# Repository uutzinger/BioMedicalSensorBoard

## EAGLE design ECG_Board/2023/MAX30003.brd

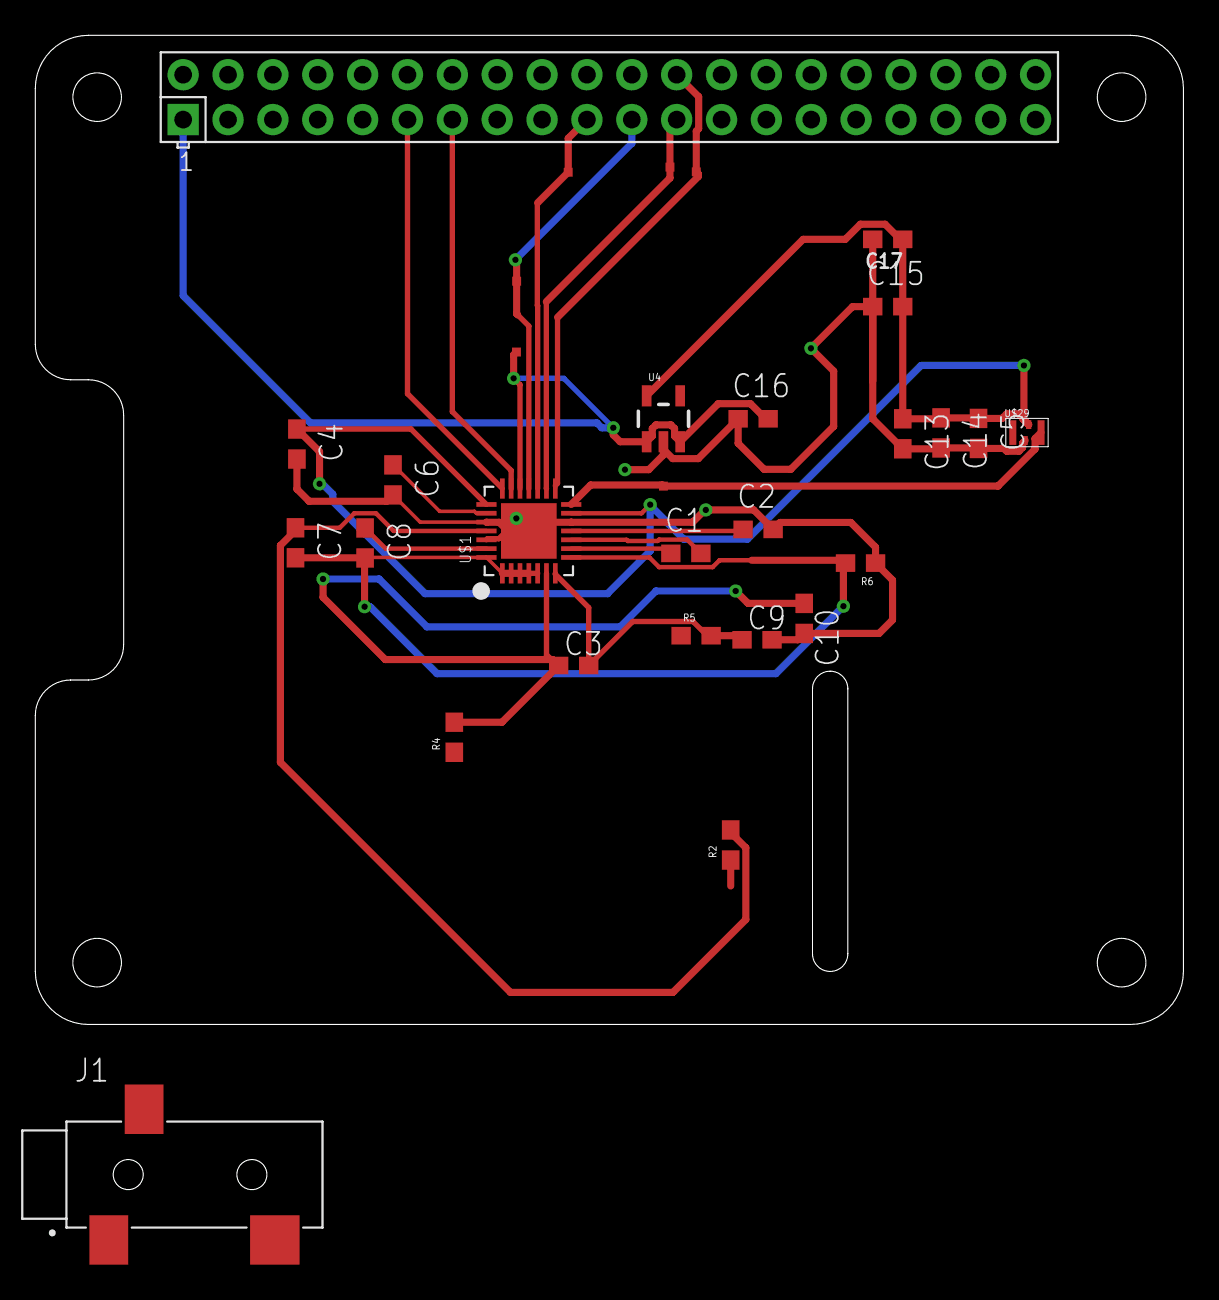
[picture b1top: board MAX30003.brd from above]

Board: 2 copper layers, 65.0 x 56.0 mm, 30 parts (0 on the bottom side), 22 nets.

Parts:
C1, C5, C8, C13, C15, C16, C17: 1.0uF; 0603
C2, C3, C9, C10: 1nF; 0603
C4, C6, C7, C14: 10uF; 0603
J1: SJ-3523-SMT-TR; CUI_SJ-3523-SMT-TR
R2, R6: 0.05; 0603
R4, R5: 47k; 0603
TP1, TP2, TP3, TP5, TP6, TP8: TEST-POINT2; PAD.02X.02
U4: AP2112K-1.8V; SOT23-5
U$1: MAX30003CTI+; QFN-28
U$29: SIT1533
X1: RASPI_BOARD_B+_HDC; RASPI_BOARD_B+HAT_DF_CF

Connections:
+1.8V: C4.1, C5.1, C13.1, C14.1, C15.2, C17.1, U4.5, U$1.13, U$1.22, U$29.4
AGND: C7.2, C8.2, R6.2, U$1.1, U$1.2, U$1.3, U$1.4, U$1.5, U$1.8, U$1.28
CSB: TP3.P$1, U$1.15, X1.24
ECGN: C3.2, C9.1, R5.2, U$1.7
ECGP: C3.1, C10.1, R4.2, U$1.6
FCLK: TP5.P$1, U$1.14, U$29.3, X1.7
GND: C2.2, C4.2, C5.2, C6.2, C9.2, C10.2, C13.2, C14.2, C15.1, C16.1, C17.2, R6.1, U4.2, U$1.12, U$1.24, U$1.26, U$1.THERMAL, U$29.2
INT2B: U$1.20, X1.13
INTB: U$1.21, X1.11
MISO: TP2.P$1, U$1.18, X1.21
MOSI: TP1.P$1, U$1.17, X1.19
unnamed: J1.3, R4.1
unnamed: C6.1, U$1.23
unnamed: C1.1, U$1.9
unnamed: J1.1, R2.1
unnamed: C1.2, U$1.10
unnamed: C2.1, U$1.11
unnamed: J1.2, R5.1
unnamed: C8.1, U$1.27
SCLK: TP8.P$1, U$1.16, X1.23
VCM: C7.1, R2.2, U$1.25
VDD: C16.2, TP6.P$1, U4.1, U4.3, U$1.19, X1.1

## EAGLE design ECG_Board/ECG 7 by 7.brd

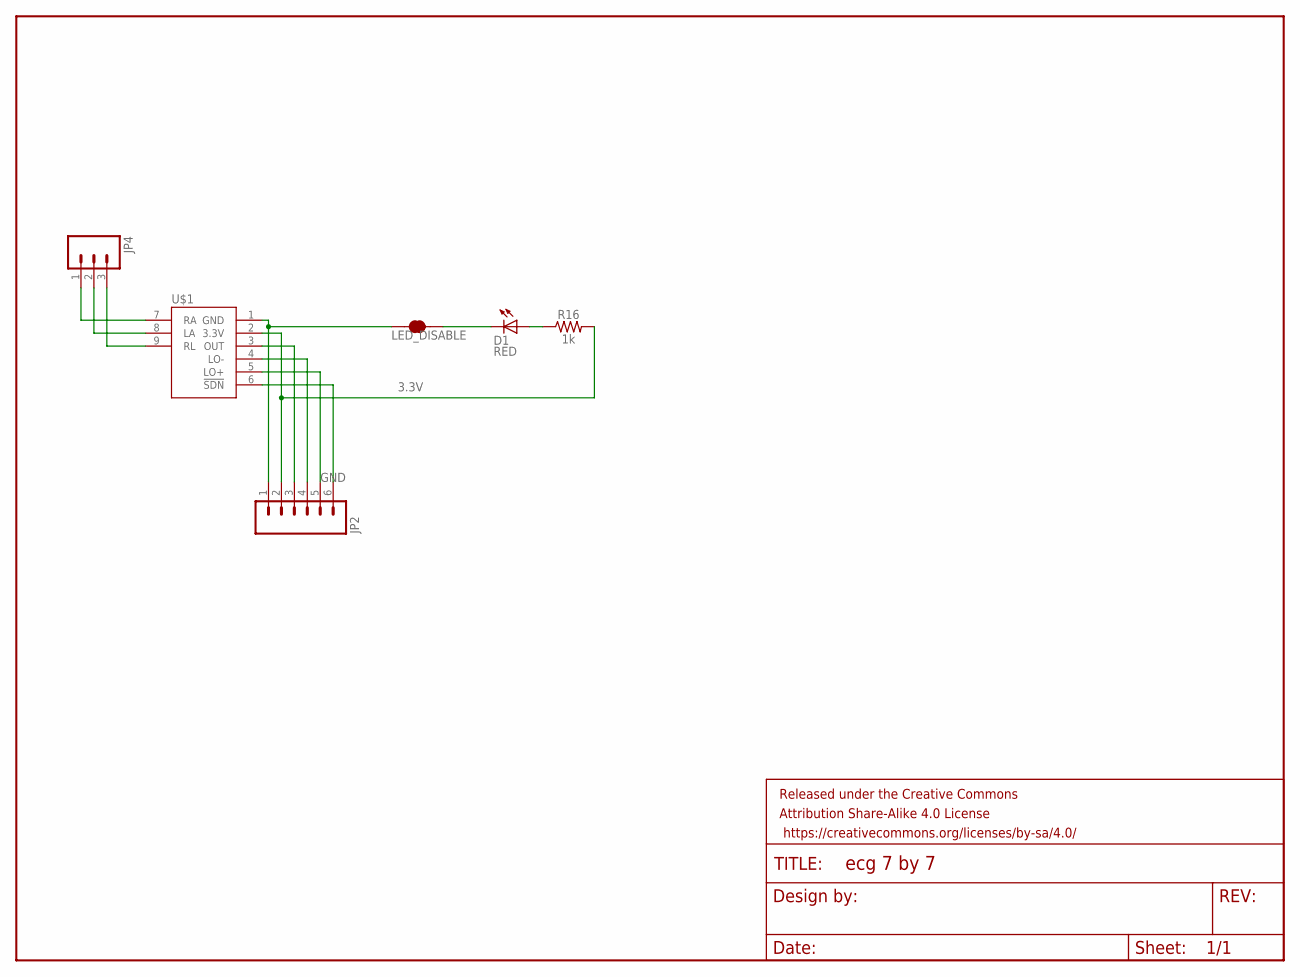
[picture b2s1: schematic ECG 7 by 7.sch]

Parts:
D1: RED; LED-0603
FRAME1: FRAME-LETTERNO_PACKAGE; DUMMY
JP2: M06SIP; 1X06
JP4: M03PTH; 1X03
LED_DISABLE: JUMPER-SMT_2_NC_TRACE_SILK; SMT-JUMPER_2_NC_TRACE_SILK
R16: 1k; 0603
U$1: SPARK_ECG

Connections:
3.3V: JP2.2, R16.2, U$1.2 (3.3V)
GND: JP2.1, LED_DISABLE.1, U$1.1 (GND)
unnamed: JP4.1, U$1.7 (RA)
unnamed: JP4.2, U$1.8 (LA)
unnamed: JP4.3, U$1.9 (RL)
unnamed: JP2.6, U$1.6 (!SDN)
unnamed: JP2.5, U$1.5 (LO+)
unnamed: JP2.4, U$1.4 (LO-)
unnamed: JP2.3, U$1.3 (OUT)
unnamed: D1.A, R16.1
unnamed: D1.C, LED_DISABLE.2

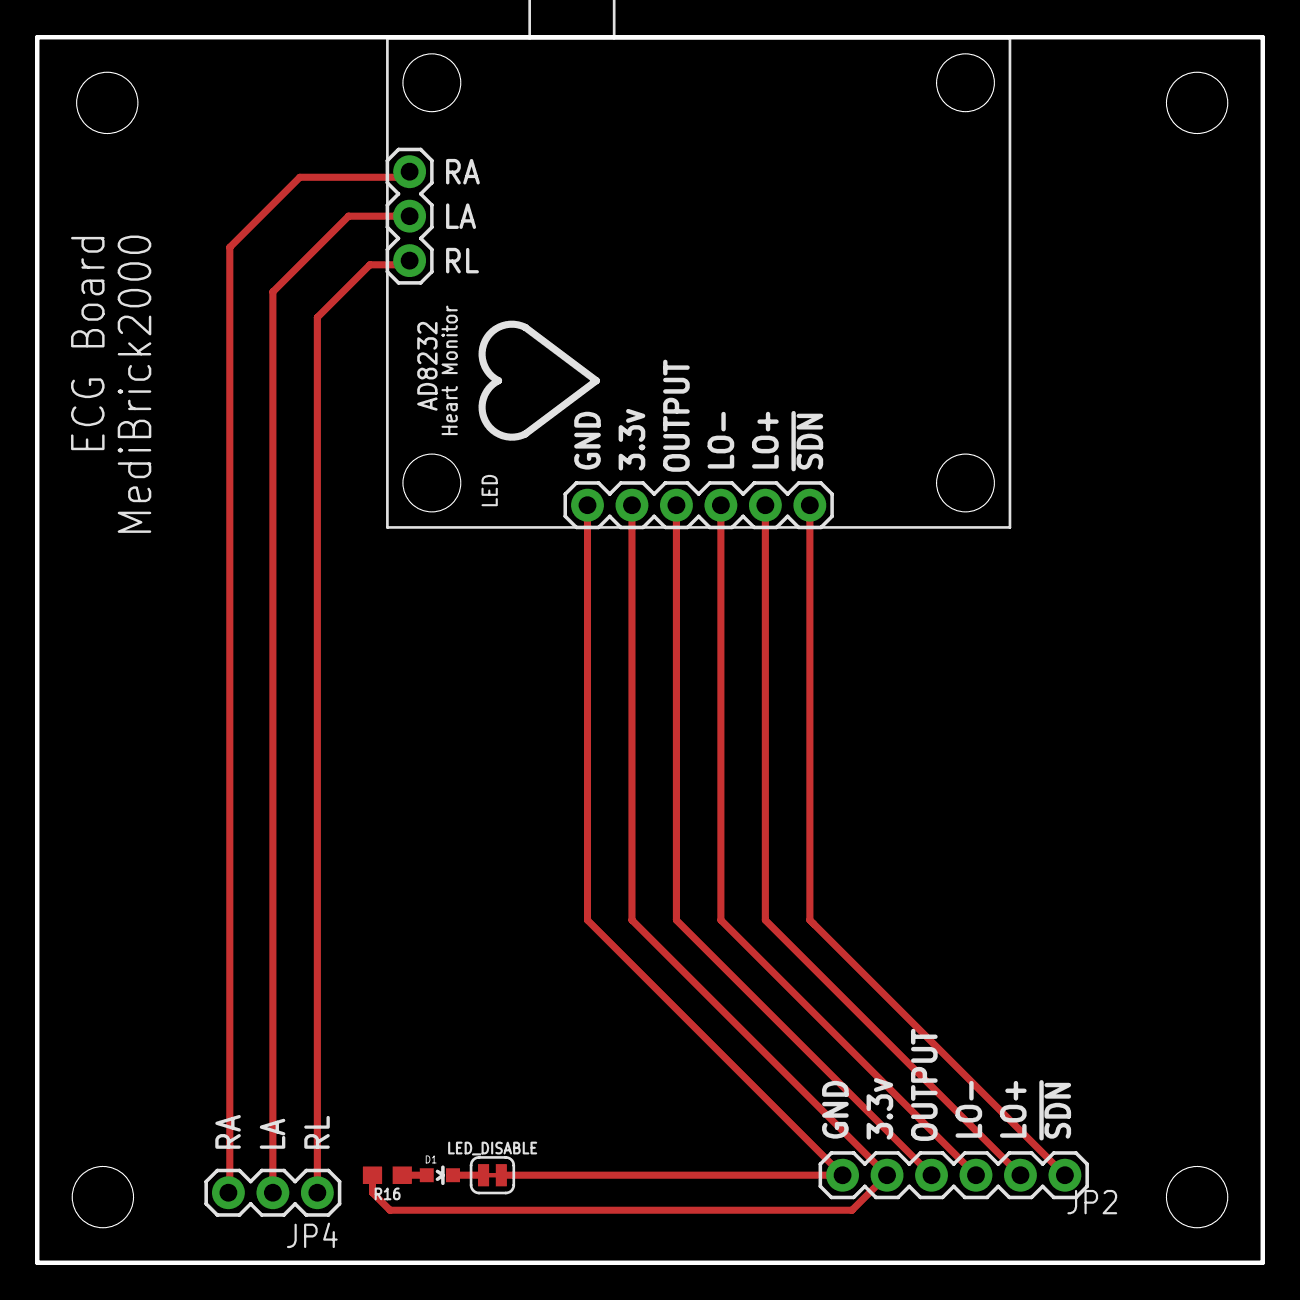
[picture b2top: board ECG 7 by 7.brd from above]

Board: 2 copper layers, 70.0 x 70.0 mm, 7 parts (0 on the bottom side), 11 nets.

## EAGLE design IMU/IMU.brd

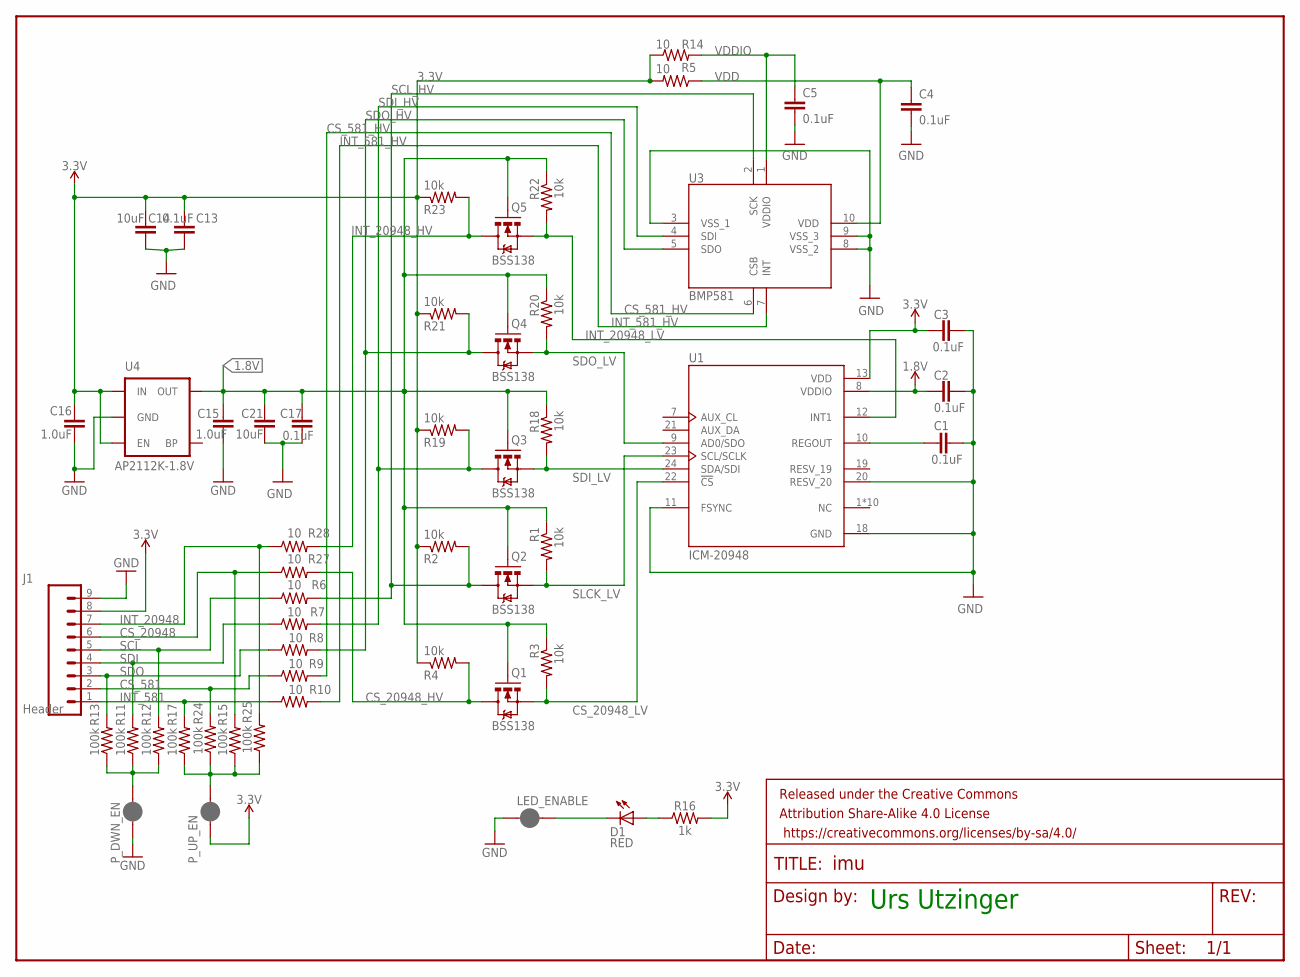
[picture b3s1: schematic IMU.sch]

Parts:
C1, C2, C3, C4, C5, C13, C17: 0.1uF; 0603
C14, C21: 10uF; 0603@1
C15, C16: 1.0uF; 0603
D1: RED; LED-0603
FRAME1: FRAME-LETTERNO_PACKAGE; DUMMY
J1: Header; 1X09
LED_ENABLE: LED ENABLE; SMT-JUMPER_2_NC_PASTE_SILK
P_DWN_EN: JUMPER-SMT_2_NC_PASTE_SILK; SMT-JUMPER_2_NC_PASTE_SILK
P_UP_EN: JUMPER-SMT_2_NC_PASTE_SILK; SMT-JUMPER_2_NC_PASTE_SILK
Q1, Q2, Q3, Q4, Q5: BSS138; SPARKFUN_SOT23-3
R1, R2, R3, R4, R18, R19, R20, R21, R22, R23: 10k; 0603
R5, R6, R7, R8, R9, R10, R14, R27, R28: 10; 0603
R11, R12, R13, R15, R17, R24, R25: 100k; 0603
R16: 1k; 0603
U1: ICM-20948; QFN40P300X300X105-24N
U3: BMP581
U4: AP2112K-1.8V; SOT23-5

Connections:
1.8V: C2.1, C15.2, C17.1, C21.1, Q1.1 (G), Q2.1 (G), Q3.1 (G), Q4.1 (G), Q5.1 (G), R1.1, R3.1, R18.1, R20.1, R22.1, U1.8 (VDDIO), U4.5 (OUT)
3.3V: C3.1, C13.1, C14.1, C16.2, J1.8, P_UP_EN.1, R2.1, R4.1, R5.2, R14.1, R16.2, R19.1, R21.1, R23.1, U1.13 (VDD), U4.1 (IN), U4.3 (EN)
CS_581: J1.2, R9.1, R24.2
CS_581_HV: R9.2, U3.6 (CSB)
CS_20948: J1.6, R15.2, R27.1
CS_20948_HV: Q1.3 (D), R4.2, R27.2
CS_20948_LV: Q1.2 (S), R3.2, U1.22 (!CS)
GND: C1.2, C2.2, C3.2, C4.2, C5.2, C13.2, C14.2, C15.1, C16.1, C17.2, C21.2, J1.9, LED_ENABLE.1, P_DWN_EN.1, U1.11 (FSYNC), U1.18 (GND), U1.20 (RESV_20), U3.3 (VSS_1), U3.8 (VSS_2), U3.9 (VSS_3), U4.2 (GND)
INT_581: J1.1, R10.1, R17.2
INT_581_HV: R10.2, U3.7 (INT)
INT_20948: J1.7, R25.2, R28.1
INT_20948_HV: Q5.3 (D), R23.2, R28.2
INT_20948_LV: Q5.2 (S), R22.2, U1.12 (INT1)
unnamed: C1.1, U1.10 (REGOUT)
unnamed: D1.A, R16.1
unnamed: D1.C, LED_ENABLE.2
unnamed: P_DWN_EN.2, R11.1, R12.1, R13.1
unnamed: P_UP_EN.2, R15.1, R17.1, R24.1, R25.1
SCL: J1.5, R6.1, R12.2
SCL_HV: Q2.3 (D), R2.2, R6.2, U3.2 (SCK)
SDI: J1.4, R7.1, R11.2
SDI_HV: Q3.3 (D), R7.2, R19.2, U3.4 (SDI)
SDI_LV: Q3.2 (S), R18.2, U1.24 (SDA/SDI)
SDO: J1.3, R8.1, R13.2
SDO_HV: Q4.3 (D), R8.2, R21.2, U3.5 (SDO)
SDO_LV: Q4.2 (S), R20.2, U1.9 (AD0/SDO)
SLCK_LV: Q2.2 (S), R1.2, U1.23 (SCL/SCLK)
VDD: C4.1, R5.1, U3.10 (VDD)
VDDIO: C5.1, R14.2, U3.1 (VDDIO)

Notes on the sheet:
Urs Utzinger

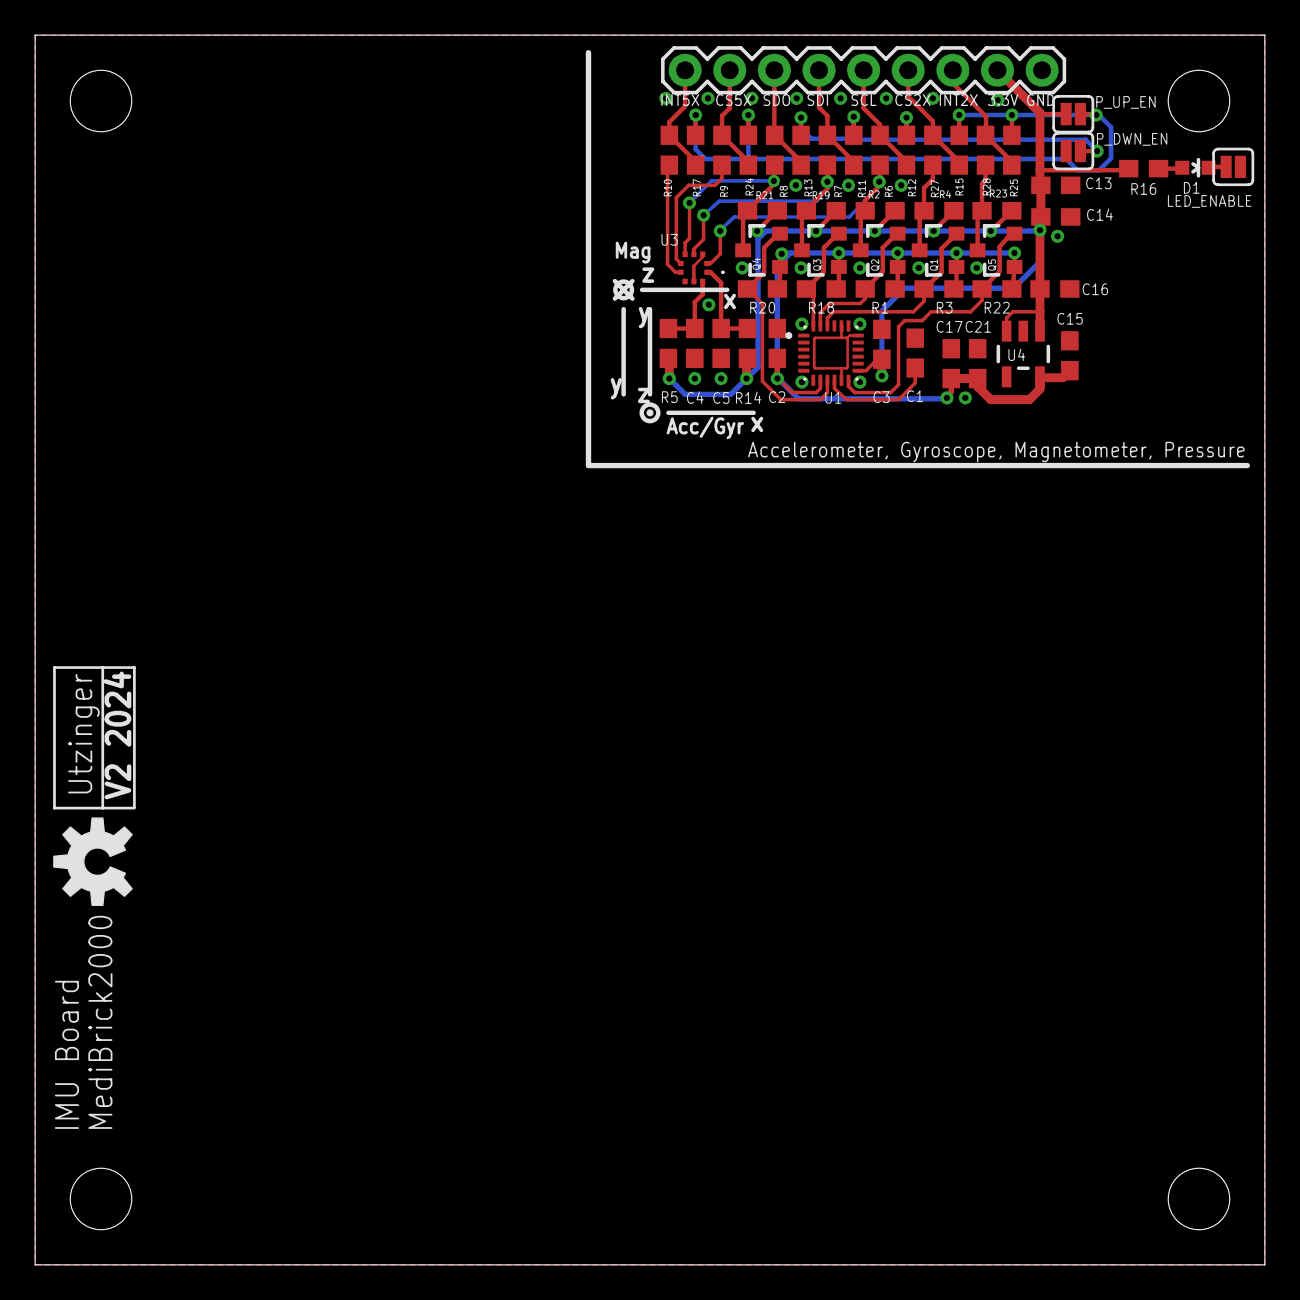
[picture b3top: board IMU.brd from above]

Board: 2 copper layers, 70.0 x 70.0 mm, 53 parts (0 on the bottom side), 29 nets.

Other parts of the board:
U$1: OSHW-LOGO-M

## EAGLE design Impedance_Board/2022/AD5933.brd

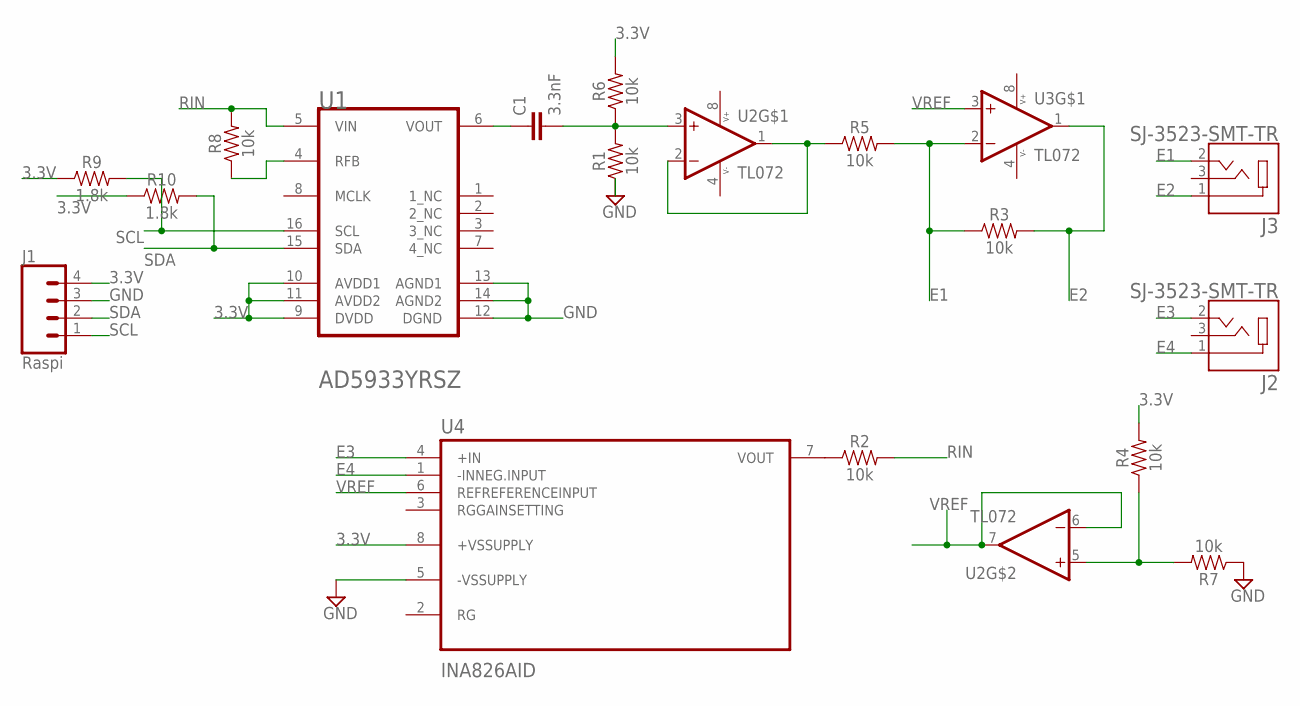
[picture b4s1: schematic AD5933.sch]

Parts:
C1: 3.3nF; 0603
J1: Raspi; 1X04
J2, J3: SJ-3523-SMT-TR; CUI_SJ-3523-SMT-TR
R1, R2, R3, R4, R5, R6, R7, R8: 10k; 0603
R9, R10: 1.8k; 0603
U1: ANALOG_DEVICES_AD5933YRSZANALOG_DEVICES_AD5933YRS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; ANALOG_DEVICES_AD5933YRSZ_0
U2, U3: TL072; SOIC127P600X175-8N
U4: INA826AID; SOIC127P599X175-8N

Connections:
3.3V: J1.4, R4.2, R6.2, R9.1, R10.1, U1.9 (DVDD), U1.10 (AVDD1), U1.11 (AVDD2), U4.8 (+VSSUPPLY)
E1: J3.2, R3.1, R5.2, U3.2 (-IN1)
E2: J3.1, R3.2, U3.1 (OUT1)
E3: J2.2, U4.4 (+IN)
E4: J2.1, U4.1 (-INNEG.INPUT)
GND: J1.3, R1.1, R7.1, U1.12 (DGND), U1.13 (AGND1), U1.14 (AGND2), U4.5 (-VSSUPPLY)
unnamed: R2.1, U4.7 (VOUT)
unnamed: C1.1, U1.6 (VOUT)
unnamed: C1.2, R1.2, R6.1, U2.3 (+IN1)
unnamed: R5.1, U2.1 (OUT1), U2.2 (-IN1)
unnamed: R8.1, U1.4 (RFB)
unnamed: R4.1, R7.2, U2.5 (+IN2)
RIN: R2.2, R8.2, U1.5 (VIN)
SCL: J1.1, R9.2, U1.16 (SCL)
SDA: J1.2, R10.2, U1.15 (SDA)
V+: U2.8 (V+), U3.8 (V+)
V-: U2.4 (V-), U3.4 (V-)
VREF: U2.6 (-IN2), U2.7 (OUT2), U3.3 (+IN1), U4.6 (REFREFERENCEINPUT)

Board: 2 copper layers, 18 parts (0 on the bottom side), 18 nets, no tracks yet.

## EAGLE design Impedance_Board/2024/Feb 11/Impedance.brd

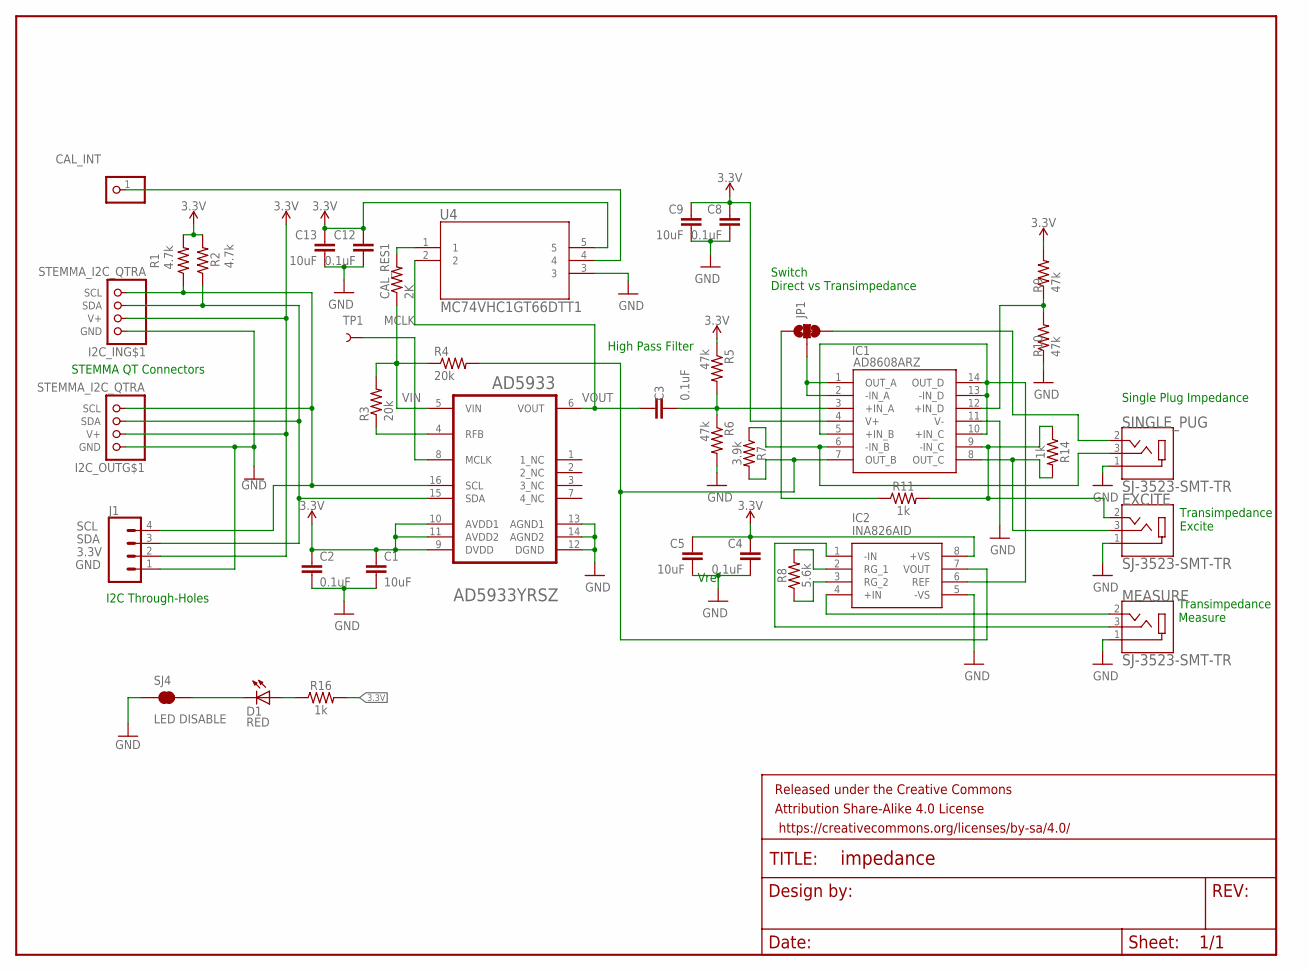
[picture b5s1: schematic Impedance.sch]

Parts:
AD5933: ANALOG_DEVICES_AD5933YRSZANALOG_DEVICES_AD5933YRS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; ANALOG_DEVICES_AD5933YRSZ_0
C1, C5, C9, C13: 10uF; C0603
C2, C4, C8, C12: 0.1uF; C0603
C3: 0.1uF; 0603
CAL_INT: PINHD-1X1; 1X01
CAL_RES1: 2K; R0603
D1: RED; LED-0603
EXCITE: SJ-3523-SMT-TR; CUI_SJ-3523-SMT-TR
FRAME1: FRAME-LETTERNO_PACKAGE; DUMMY
I2C_IN, I2C_OUT: STEMMA_I2C_QTRA; JST_SH4_RA
IC1: AD8608ARZ; SOIC127P600X175-14N
IC2: INA826AID; SOIC127P600X175-8N
J1: CONN_04; 1X04
JP1: JUMPER-SMT_3_1-NC_TRACE_NO-SILK; SMT-JUMPER_3_1-NC_TRACE_NO-SILK
MEASURE: SJ-3523-SMT-TR; CUI_SJ-3523-SMT-TR
R1, R2: 4.7k; 0603
R3, R4: 20k; 0603
R5, R6, R9, R10: 47k; 0603
R7: 3.9k; 0603
R8: 5.6k; 0603
R11, R14, R16: 1k; 0603
SINGLE_PUG: SJ-3523-SMT-TR; CUI_SJ-3523-SMT-TR
SJ4: LED DISABLE; SMT-JUMPER_2_NC_TRACE_NO-SILK
TP1: TEST-POINT3X5; PAD.03X.05
U4: MC74VHC1GT66DTT1; TSOP5_1P65X3P15_ONS

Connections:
3.3V: AD5933.9 (DVDD), AD5933.10 (AVDD1), AD5933.11 (AVDD2), C1.1, C2.1, C4.1, C5.1, C8.1, C9.1, C12.1, C13.1, I2C_IN.2 (V+), I2C_OUT.2 (V+), IC1.4 (V+), IC2.8 (+VS), J1.2, R1.2, R2.2, R5.1, R9.2, R16.2, U4.5
GND: AD5933.12 (DGND), AD5933.13 (AGND1), AD5933.14 (AGND2), C1.2, C2.2, C4.2, C5.2, C8.2, C9.2, C12.2, C13.2, EXCITE.1, I2C_IN.1 (GND), I2C_OUT.1 (GND), IC1.11 (V-), IC2.5 (-VS), J1.1, MEASURE.1, R6.2, R10.1, SINGLE_PUG.1, SJ4.1, U4.3
MCLK: AD5933.8 (MCLK), TP1.P$1
unnamed: IC1.6 (-IN_B), R7.1, SINGLE_PUG.3
unnamed: CAL_INT.1, U4.4
unnamed: AD5933.4 (RFB), R3.1
unnamed: C3.2, IC1.3 (+IN_A), R5.2, R6.1
unnamed: JP1.1, R11.1
unnamed: IC1.1 (OUT_A), IC1.2 (-IN_A), JP1.2
unnamed: IC1.7 (OUT_B), IC2.7 (VOUT), R4.2, R7.2
unnamed: IC1.12 (+IN_D), R9.1, R10.2
unnamed: JP1.3, SINGLE_PUG.2
unnamed: IC1.5 (+IN_B), IC1.10 (+IN_C), IC1.13 (-IN_D), IC1.14 (OUT_D), IC2.6 (REF)
unnamed: EXCITE.2, IC1.9 (-IN_C), R11.2, R14.1
unnamed: IC2.4 (+IN), MEASURE.2
unnamed: IC2.1 (-IN), MEASURE.3
unnamed: IC2.2 (RG_1), R8.2
unnamed: IC2.3 (RG_2), R8.1
unnamed: CAL_RES1.2, U4.1
unnamed: EXCITE.3, IC1.8 (OUT_C), R14.2
unnamed: D1.A, R16.1
unnamed: D1.C, SJ4.2
SCL: AD5933.16 (SCL), I2C_IN.4 (SCL), I2C_OUT.4 (SCL), J1.4, R1.1
SDA: AD5933.15 (SDA), I2C_IN.3 (SDA), I2C_OUT.3 (SDA), J1.3, R2.1
VIN: AD5933.5 (VIN), CAL_RES1.1, R3.2, R4.1
VOUT: AD5933.6 (VOUT), C3.1, U4.2

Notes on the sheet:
High Pass Filter
Vref
Transimpedance Measure
Transimpedance Excite
Single Plug Impedance
STEMMA QT Connectors
I2C Through-Holes
Switch Direct vs Transimpedance

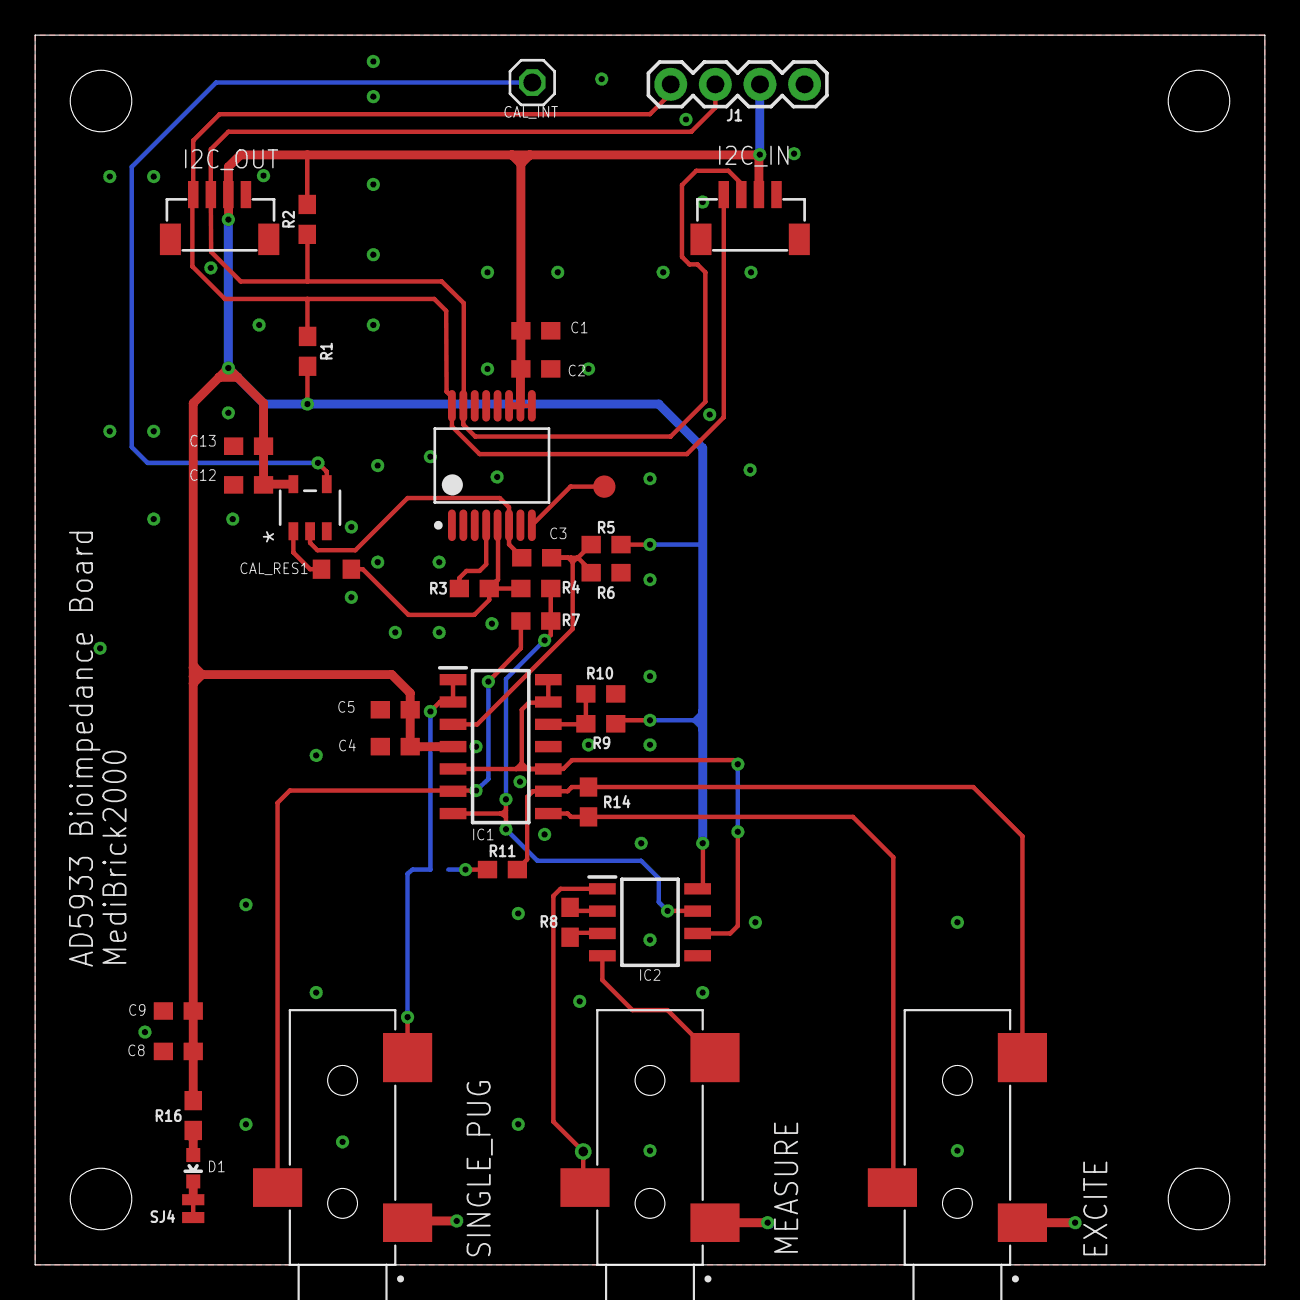
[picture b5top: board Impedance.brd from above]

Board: 2 copper layers, 70.0 x 70.0 mm, 39 parts (1 on the bottom side), 26 nets.

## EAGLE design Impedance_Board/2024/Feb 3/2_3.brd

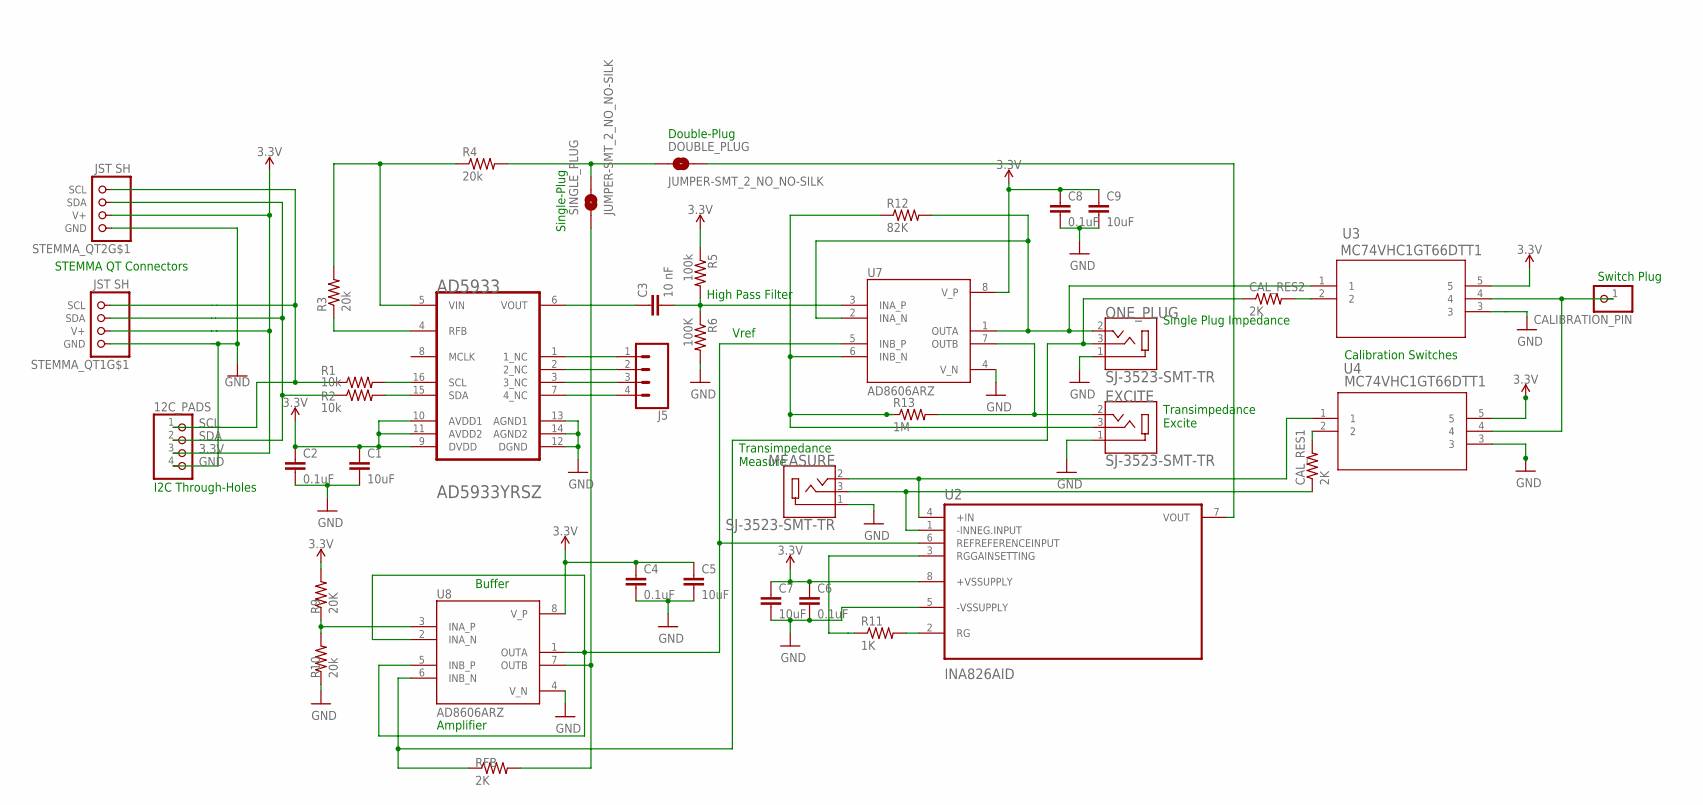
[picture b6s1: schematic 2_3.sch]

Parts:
12C_PADS: PINHD-1X4; 1X04
AD5933: ANALOG_DEVICES_AD5933YRSZANALOG_DEVICES_AD5933YRS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; ANALOG_DEVICES_AD5933YRSZ_0
C1, C5, C7, C9: 10uF; C0603
C2, C4, C6, C8: 0.1uF; C0603
C3: 10 nF; C0603
CALIBRATION_PIN: PINHD-1X1; 1X01
CAL_RES1, CAL_RES2: 2K; R0603
DOUBLE_PLUG: JUMPER-SMT_2_NO_NO-SILK; SMT-JUMPER_2_NO_NO-SILK
EXCITE: SJ-3523-SMT-TR; CUI_SJ-3523-SMT-TR
J5: CONN_04; 1X04
MEASURE: SJ-3523-SMT-TR; CUI_SJ-3523-SMT-TR
ONE_PLUG: SJ-3523-SMT-TR; CUI_SJ-3523-SMT-TR
R1, R2: 10k; R0603
R3, R4, R10: 20k; R0603
R5: 100k; R0603
R6: 100K; R0603
R9: 20K; R0603
R11: 1K; R0603
R12: 82K; R0603
R13: 1M; R0603
RFB: 2K; R0603
SINGLE_PLUG: JUMPER-SMT_2_NO_NO-SILK; SMT-JUMPER_2_NO_NO-SILK
STEMMA_QT1, STEMMA_QT2: JST SH; JST_SH4_RA
U2: INA826AID; SOIC127P599X175-8N
U3, U4: MC74VHC1GT66DTT1; TSOP5_1P65X3P15_ONS
U7, U8: AD8606ARZ; SOIC127P600X175-8N

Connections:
3.3V: 12C_PADS.3, AD5933.9 (DVDD), AD5933.10 (AVDD1), AD5933.11 (AVDD2), C1.1, C2.1, C4.1, C5.1, C6.1, C7.1, C8.1, C9.1, R5.1, R9.2, STEMMA_QT1.2 (V+), STEMMA_QT2.2 (V+), U2.8 (+VSSUPPLY), U3.5, U4.5, U7.8 (V_P), U8.8 (V_P)
GND: 12C_PADS.4, AD5933.12 (DGND), AD5933.13 (AGND1), AD5933.14 (AGND2), C1.2, C2.2, C4.2, C5.2, C6.2, C7.2, C8.2, C9.2, EXCITE.1, MEASURE.1, ONE_PLUG.1, R6.2, R10.1, STEMMA_QT1.1 (GND), STEMMA_QT2.1 (GND), U2.5 (-VSSUPPLY), U3.3, U4.3, U7.4 (V_N), U8.4 (V_N)
unnamed: AD5933.16 (SCL), R1.2
unnamed: AD5933.15 (SDA), R2.2
unnamed: AD5933.1 (1_NC), J5.1
unnamed: AD5933.2 (2_NC), J5.2
unnamed: AD5933.4 (RFB), R3.1
unnamed: AD5933.5 (VIN), R3.2, R4.1
unnamed: DOUBLE_PLUG.1, R4.2, SINGLE_PLUG.2
unnamed: AD5933.6 (VOUT), C3.1
unnamed: C3.2, R5.2, R6.1, U7.3 (INA_P)
unnamed: AD5933.3 (3_NC), J5.3
unnamed: AD5933.7 (4_NC), J5.4
unnamed: RFB.2, SINGLE_PLUG.1, U8.7 (OUTB)
unnamed: U2.6 (REFREFERENCEINPUT), U7.5 (INB_P), U8.1 (OUTA), U8.2 (INA_N), U8.5 (INB_P)
unnamed: R9.1, R10.2, U8.3 (INA_P)
unnamed: ONE_PLUG.2, R12.2, U3.1, U7.1 (OUTA), U7.2 (INA_N)
unnamed: R11.1, U2.3 (RGGAINSETTING)
unnamed: CAL_RES2.1, ONE_PLUG.3, RFB.1, U8.6 (INB_N)
unnamed: R11.2, U2.2 (RG)
unnamed: EXCITE.2, R13.2, U7.7 (OUTB)
unnamed: MEASURE.2, U2.4 (+IN), U4.1
unnamed: CAL_RES1.1, MEASURE.3, U2.1 (-INNEG.INPUT)
unnamed: CAL_RES2.2, U3.2
unnamed: EXCITE.3, R12.1, R13.1, U7.6 (INB_N)
unnamed: CAL_RES1.2, U4.2
unnamed: DOUBLE_PLUG.2, U2.7 (VOUT)
unnamed: CALIBRATION_PIN.1, U3.4, U4.4
SCL: 12C_PADS.1, R1.1, STEMMA_QT1.4 (SCL), STEMMA_QT2.4 (SCL)
SDA: 12C_PADS.2, R2.1, STEMMA_QT1.3 (SDA), STEMMA_QT2.3 (SDA)

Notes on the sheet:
High Pass Filter
Vref
Transimpedance Measure
Transimpedance Excite
Single Plug Impedance
Amplifier
Buffer
Switch Plug
Calibration Switches
STEMMA QT Connectors
I2C Through-Holes
Single-Plug
Double-Plug

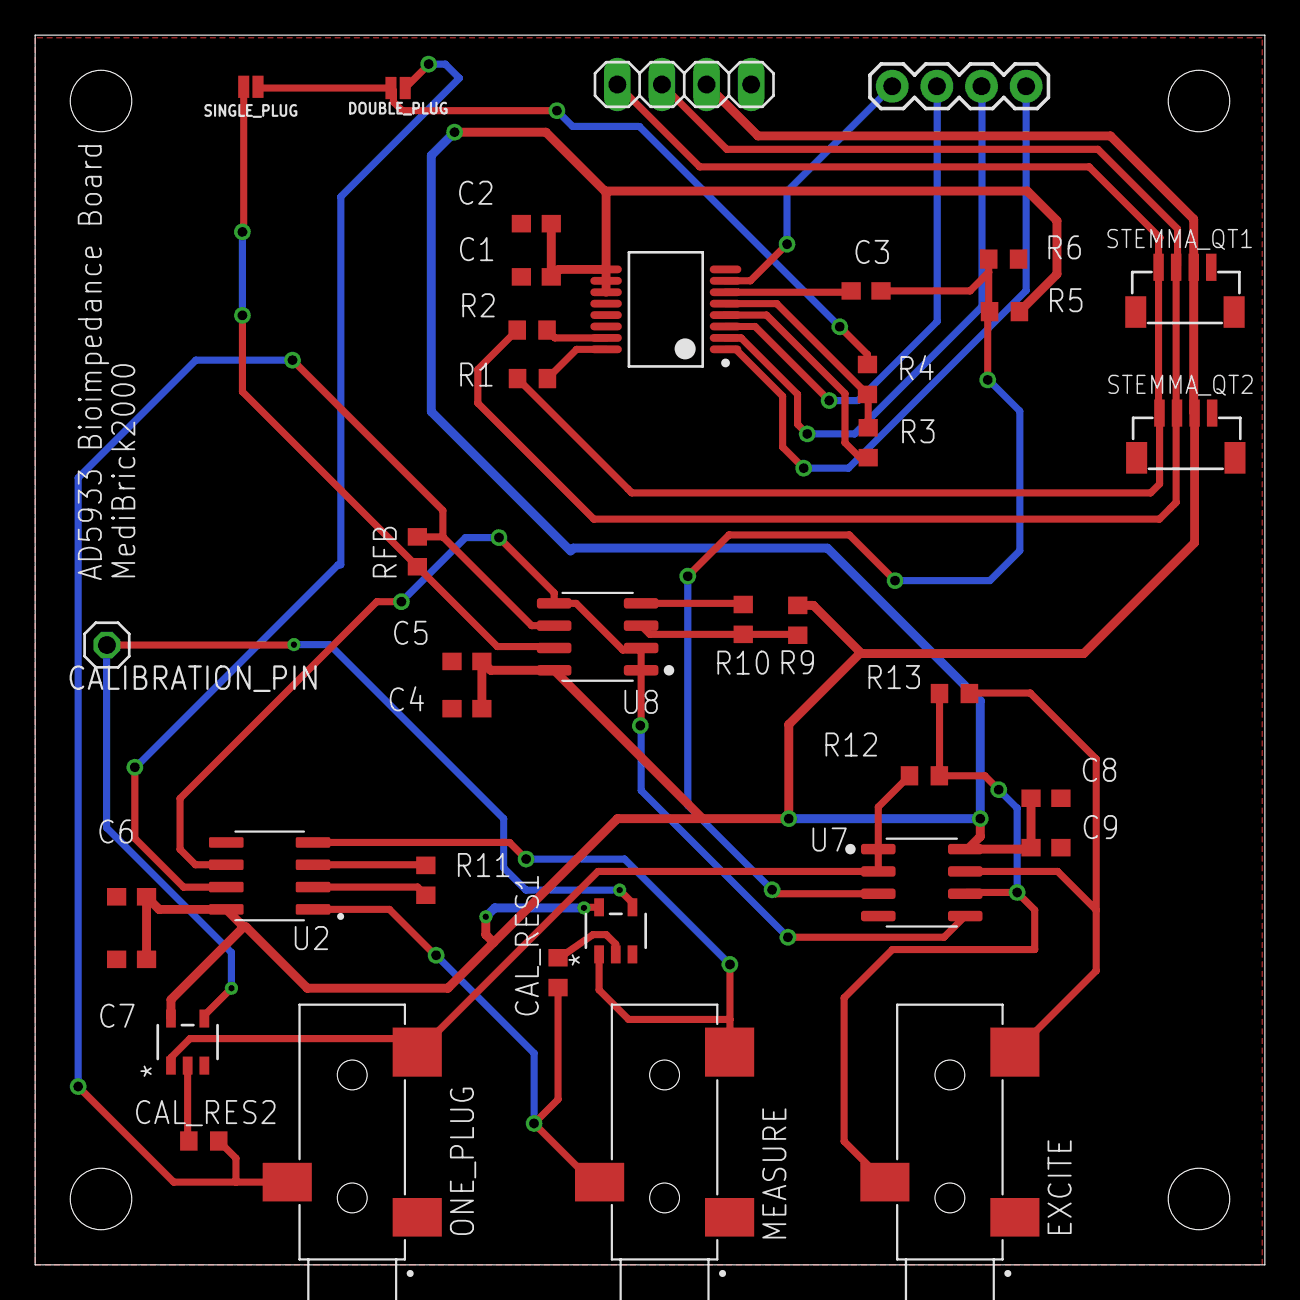
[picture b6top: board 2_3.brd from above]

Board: 2 copper layers, 70.0 x 70.0 mm, 39 parts (0 on the bottom side), 30 nets.

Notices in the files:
parts and their libraries:
SparkFun-PowerIC: Licensing: Creative Commons ShareAlike 4.0 International - https://creativecommons.org/licenses/by-sa/4.0
SparkFun-Connectors: Licensing: CC v3.0 Share-Alike You are welcome to use this library for commercial purposes.
SparkFun-Aesthetics: Released under the Creative Commons
